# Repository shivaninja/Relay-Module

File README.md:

# Relay Module (VCC–GND–SIG) | KiCad Design
## Overview

This project is a custom-designed relay module developed using KiCad, intended for microcontroller-based control of high-voltage or high-current loads. The module provides a simple 3-pin control interface (VCC, GND, SIG) and standard relay output terminals (NO, NC, COM), making it compatible with platforms such as Arduino, ESP32, and STM32.

The design focuses on simplicity, reliability, and ease of integration in embedded systems.

## Features

3-pin control interface: VCC, GND, SIG

Relay output terminals:

NO (Normally Open)

NC (Normally Closed)

COM (Common)

Transistor-based relay driving circuit

Flyback diode protection for relay coil

Compact PCB layout

Designed fully in KiCad (schematic + PCB)

## Pin Description
Control Header
Pin	Description
VCC	Supply voltage for relay module
SIG	Control signal from MCU GPIO
GND	Ground
Relay Output Terminal
Terminal	Function
NO	Connected to COM when relay is energized
NC	Connected to COM when relay is not energized
COM	Common contact

## Working Principle

The SIG pin controls a transistor that drives the relay coil.

When the control signal is asserted, the relay energizes and switches the COM contact from NC to NO.

A flyback diode protects the transistor from voltage spikes generated by the relay coil.

The module allows low-voltage microcontrollers to safely control high-power loads.

## Design Tools

EDA Tool: KiCad

Design Includes:

Schematic design

PCB layout

Footprint selection

3D PCB rendering

 PCB Preview

## Applications

Home automation

Industrial control

MCU-controlled switching

Power isolation projects

Embedded systems learning & prototyping

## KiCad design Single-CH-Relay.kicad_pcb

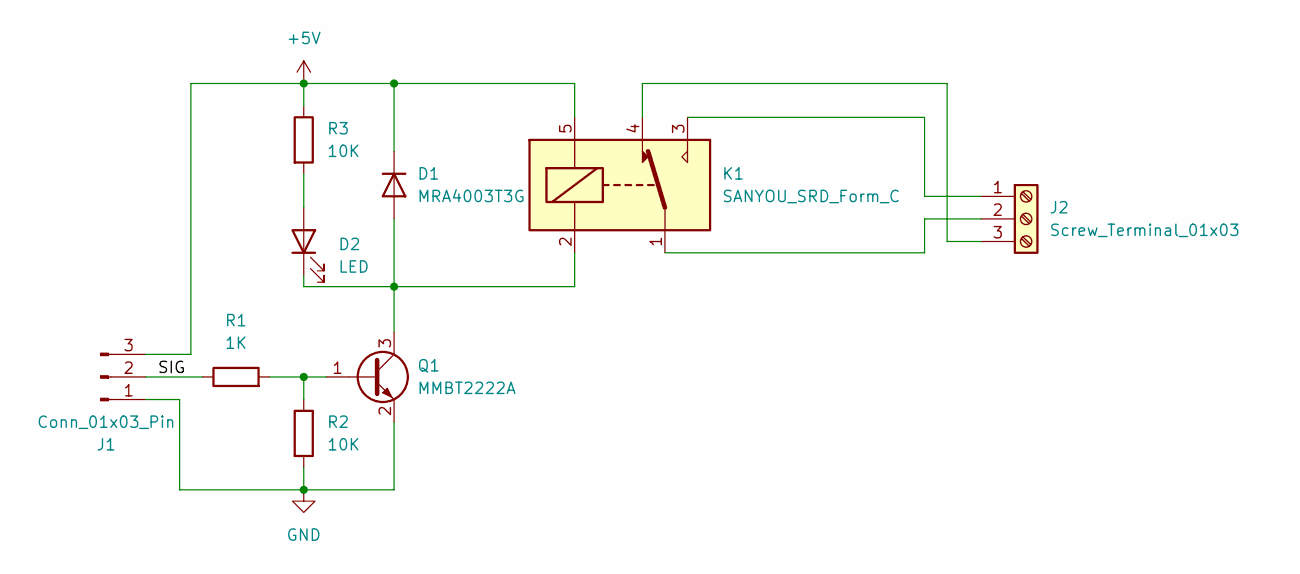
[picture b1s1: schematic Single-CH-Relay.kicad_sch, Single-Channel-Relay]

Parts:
D1: MRA4003T3G; D_SMA
D2: LED; LED_0603_1608Metric
J1: Conn_01x03_Pin; PinHeader_1x03_P2.54mm_Horizontal
J2: Screw_Terminal_01x03; TerminalBlock_bornier-3_P5.08mm
K1: SANYOU_SRD_Form_C; Relay_SPDT_SANYOU_SRD_Series_Form_C
Q1: MMBT2222A; SOT-23
R1: 1K; R_0603_1608Metric
R2, R3: 10K; R_0603_1608Metric

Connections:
+5V: D1.1 (K), J1.3, K1.5, R3.1
/SIG: J1.2, R1.1
GND: J1.1, Q1.2 (E), R2.2
unnamed: D1.2 (A), D2.1 (K), K1.2, Q1.3 (C)
unnamed: D2.2 (A), R3.2
unnamed: J2.1, K1.3
unnamed: J2.2, K1.1
unnamed: J2.3, K1.4
unnamed: Q1.1 (B), R1.2, R2.1

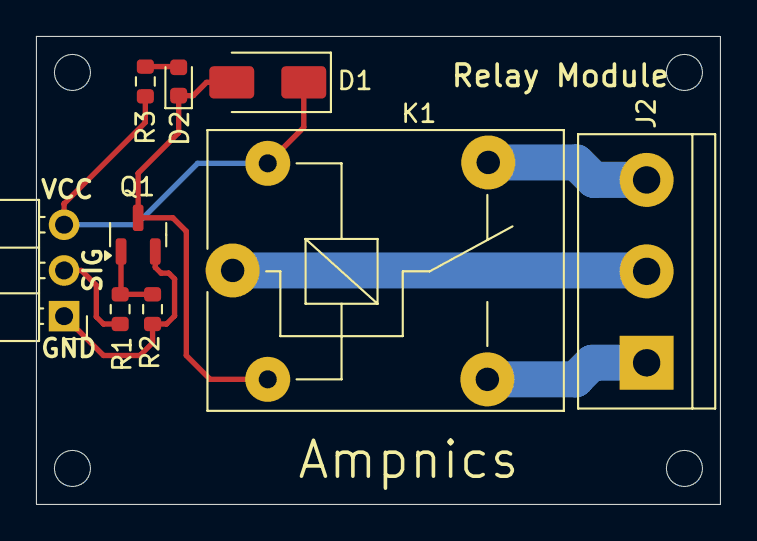
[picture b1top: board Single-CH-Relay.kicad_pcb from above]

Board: 2 copper layers, 38.0 x 26.0 mm, 9 parts (0 on the bottom side), 9 nets.
